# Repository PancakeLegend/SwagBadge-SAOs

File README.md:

# SwagBadge SAOs
 Addons for the LCA2021 SwagBadge

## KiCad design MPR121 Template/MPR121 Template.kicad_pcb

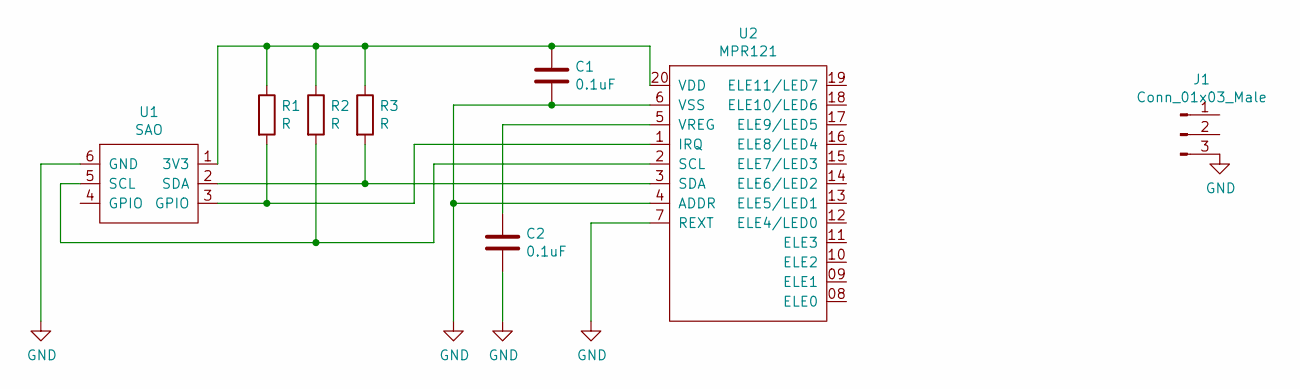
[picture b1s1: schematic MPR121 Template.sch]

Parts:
C1, C2: 0.1uF; C_0805_HandSoldering
J1: Conn_01x03_Male; Touch_Slider_Shielded
R1, R2, R3: R; R_0805_HandSoldering
U1: SAO; SAO_Header_6-Pin
U2: MPR121; SiliconLabs_QFN-20-1EP_3x3mm_Pitch0.5mm

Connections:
GND: C1.2, C2.2, J1.3, U1.6 (GND), U2.4 (ADDR), U2.6 (VSS), U2.7 (REXT)
unnamed: C1.1, R1.1, R2.1, R3.1, U1.1 (3V3), U2.20 (VDD)
unnamed: C2.1, U2.5 (VREG)
unnamed: R1.2, U1.3 (GPIO), U2.1 (IRQ)
unnamed: R2.2, U1.5 (SCL), U2.2 (SCL)
unnamed: R3.2, U1.2 (SDA), U2.3 (SDA)

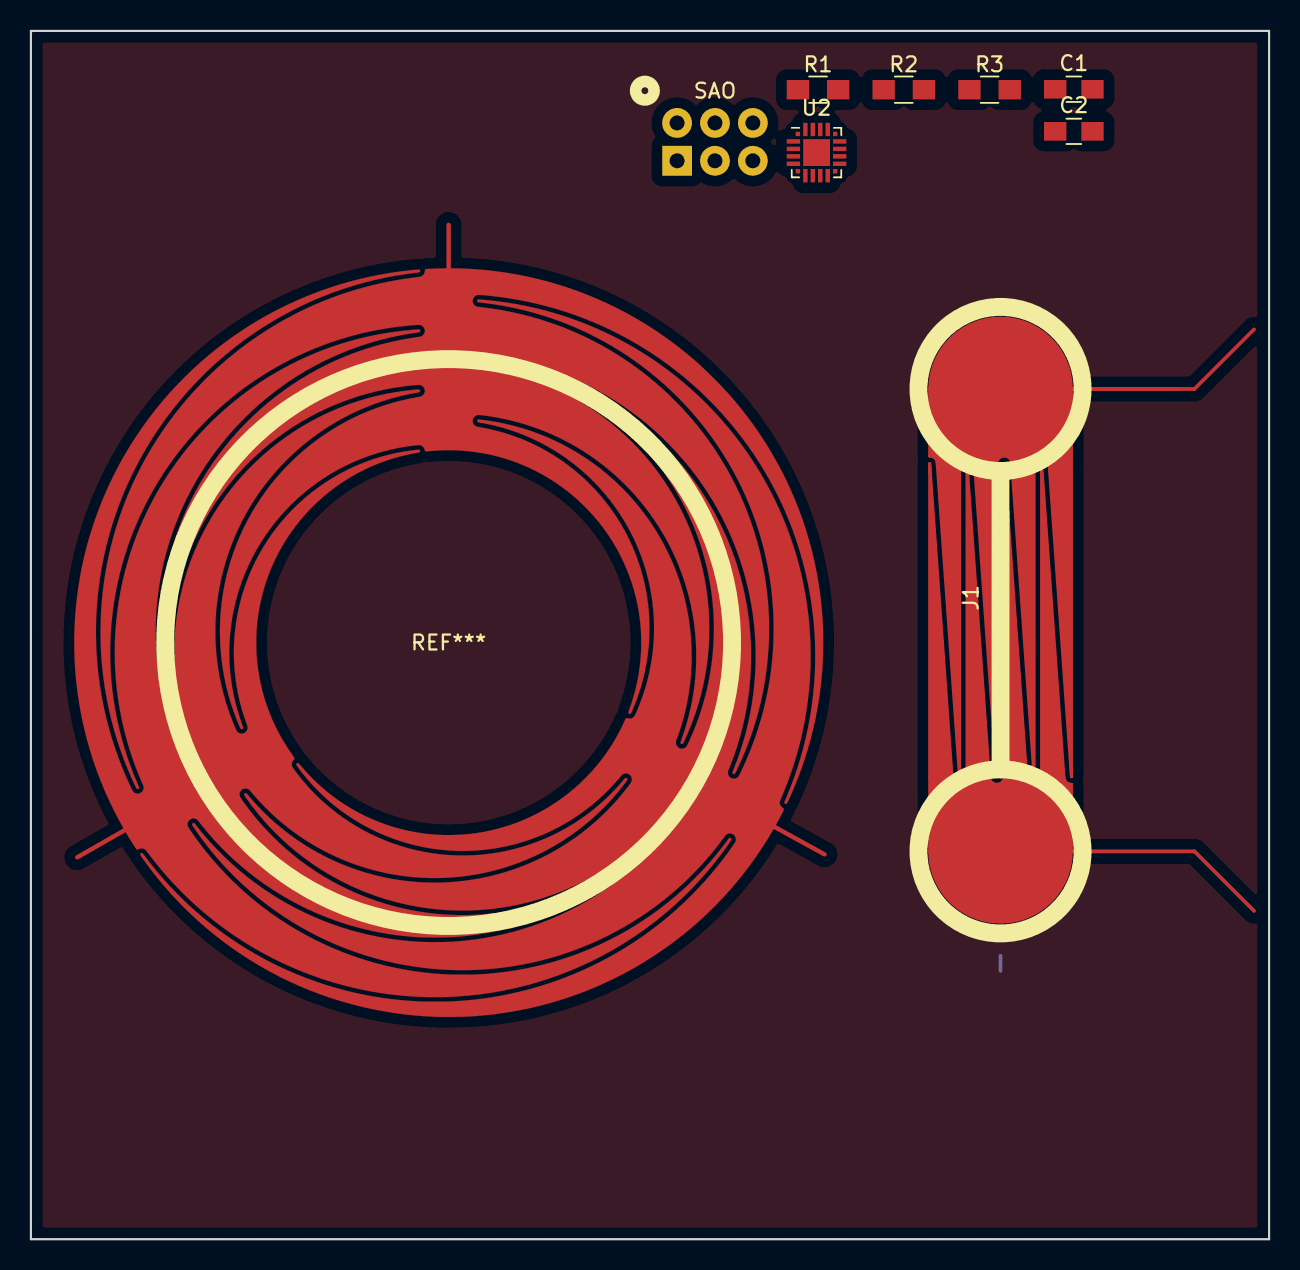
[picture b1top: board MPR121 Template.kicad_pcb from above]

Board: 2 copper layers, 83.0 x 81.0 mm, 8 parts (0 on the bottom side), 6 nets.

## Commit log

2020-10-12 Schematic added
2020-10-19 Template added
